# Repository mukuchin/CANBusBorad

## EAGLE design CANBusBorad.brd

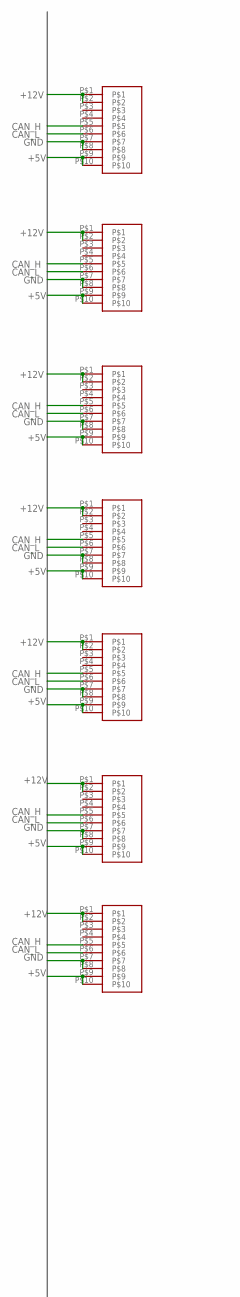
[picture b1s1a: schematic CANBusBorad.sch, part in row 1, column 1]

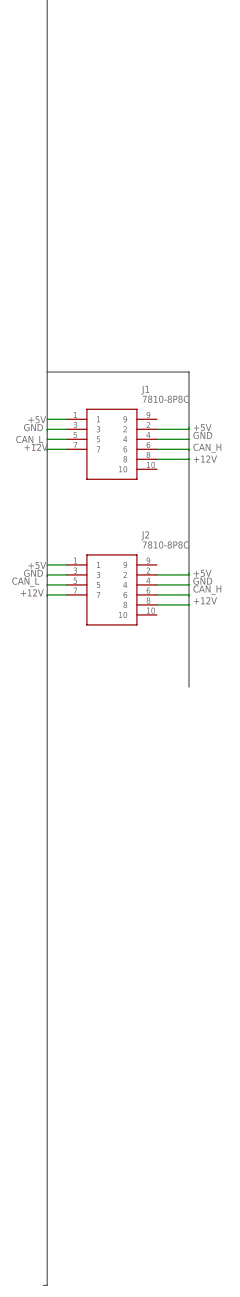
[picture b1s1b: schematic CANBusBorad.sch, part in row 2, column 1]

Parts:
CON1, CON2, CON3, CON4, CON5, CON6, CON7: FH-2X5SG/RH; BOX10P_SOCKET
J1, J2: 7810-8P8C; 78108P8C

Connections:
+5V: CON1.P$9, CON1.P$10, CON2.P$9, CON2.P$10, CON3.P$9, CON3.P$10, CON4.P$9, CON4.P$10, CON5.P$9, CON5.P$10, CON6.P$9, CON6.P$10, CON7.P$9, CON7.P$10, J1.1, J1.2, J2.1, J2.2
+12V: CON1.P$1, CON1.P$2, CON2.P$1, CON2.P$2, CON3.P$1, CON3.P$2, CON4.P$1, CON4.P$2, CON5.P$1, CON5.P$2, CON6.P$1, CON6.P$2, CON7.P$1, CON7.P$2, J1.7, J1.8, J2.7, J2.8
CAN_H: CON1.P$5, CON2.P$5, CON3.P$5, CON4.P$5, CON5.P$5, CON6.P$5, CON7.P$5, J1.6, J2.6
CAN_L: CON1.P$6, CON2.P$6, CON3.P$6, CON4.P$6, CON5.P$6, CON6.P$6, CON7.P$6, J1.5, J2.5
GND: CON1.P$7, CON1.P$8, CON2.P$7, CON2.P$8, CON3.P$7, CON3.P$8, CON4.P$7, CON4.P$8, CON5.P$7, CON5.P$8, CON6.P$7, CON6.P$8, CON7.P$7, CON7.P$8, J1.3, J1.4, J2.3, J2.4

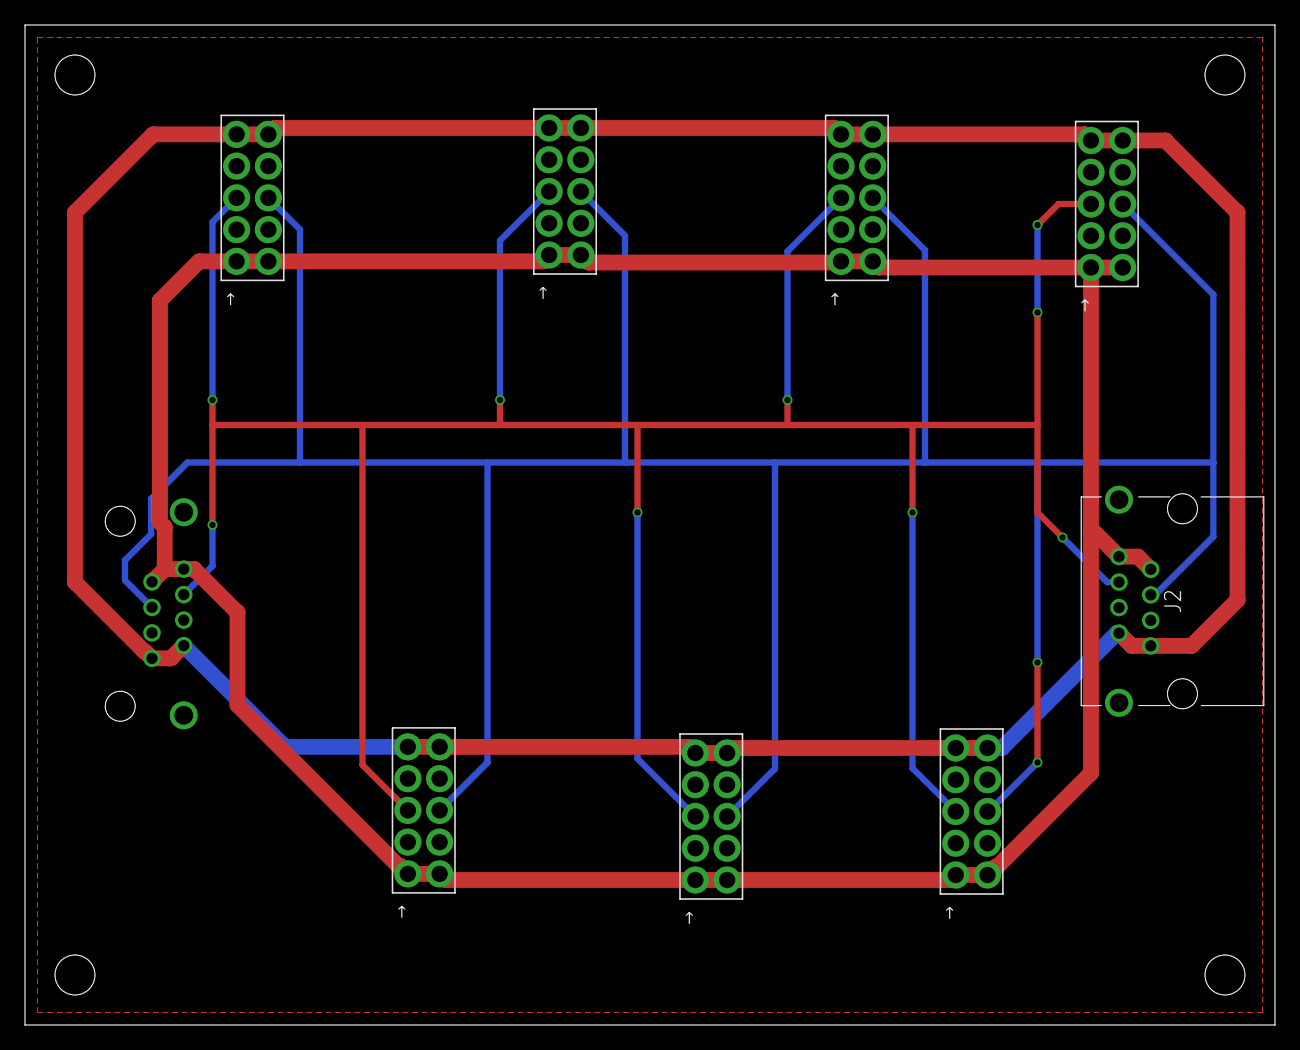
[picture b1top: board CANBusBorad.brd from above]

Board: 2 copper layers, 100.0 x 80.0 mm, 9 parts (1 on the bottom side), 5 nets.

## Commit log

2020-11-03 DesignSparkのやつをほぼそのままEagleにしました。
